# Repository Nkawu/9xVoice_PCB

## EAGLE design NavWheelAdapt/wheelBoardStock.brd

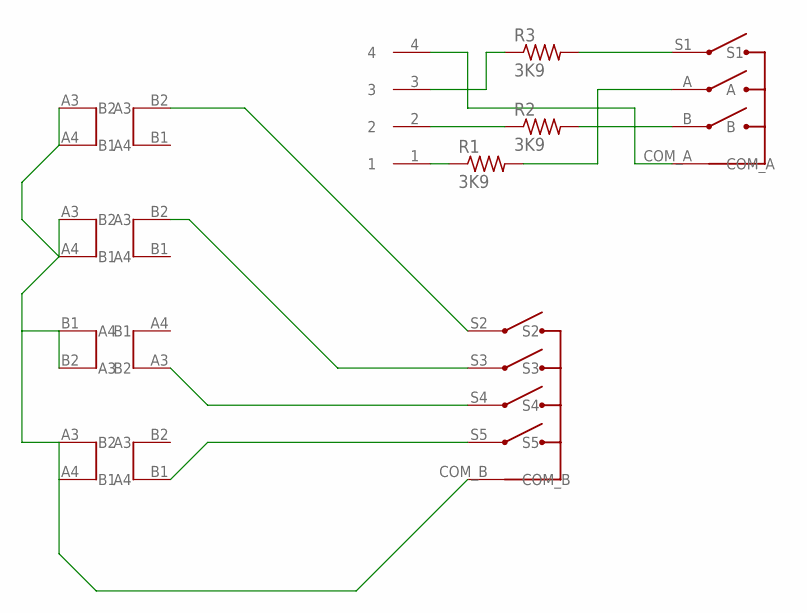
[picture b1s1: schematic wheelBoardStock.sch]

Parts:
R1, R2, R3: 3K9; R1206
U$1: TSWB-3N-CB222; W/DIREC
U$2, U$3, U$4, U$5: 9X_TACT_PATCH; 9XTACTPADS
U$6: 2MM_4P_HEADER; JST2MM_4P

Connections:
COM_A: U$1.COM_A, U$6.4
COM_B: U$1.COM_B, U$2.A3, U$2.A4, U$3.A3, U$3.A4, U$4.B1, U$4.B2, U$5.A3, U$5.A4
unnamed: R1.1, U$6.1
unnamed: R2.1, U$6.2
unnamed: R3.1, U$6.3
PHASE_A: R1.2, U$1.A
PHASE_B: R2.2, U$1.B
S2: U$1.S2, U$2.B2
S3: U$1.S3, U$3.B2
S4: U$1.S4, U$4.A3
S5: U$1.S5, U$5.B1
SELECT: R3.2, U$1.S1

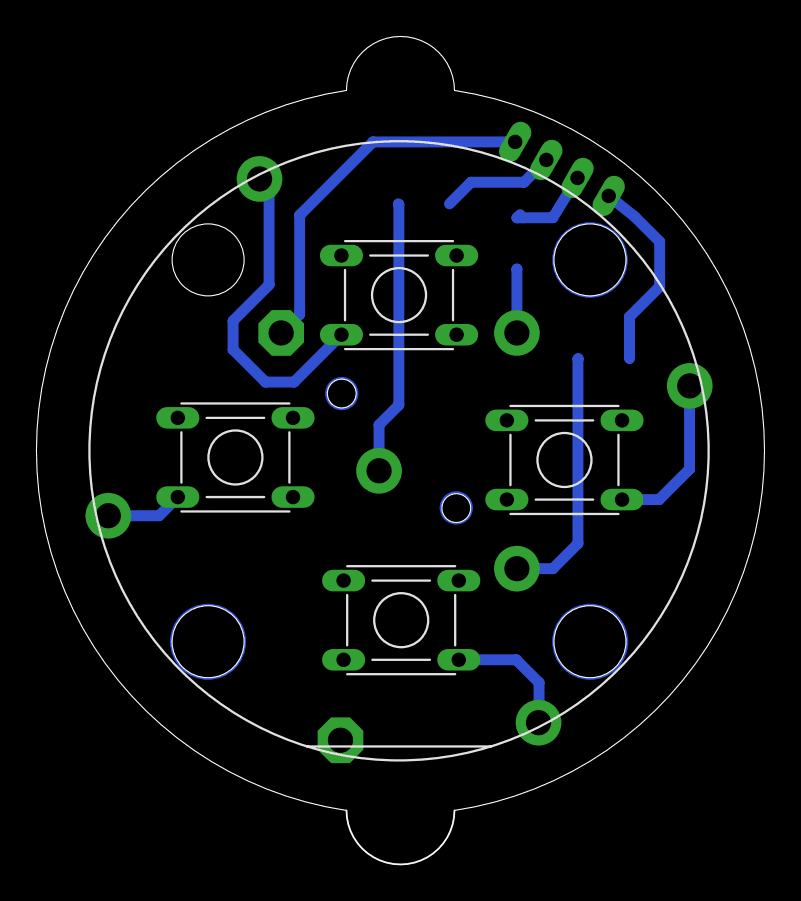
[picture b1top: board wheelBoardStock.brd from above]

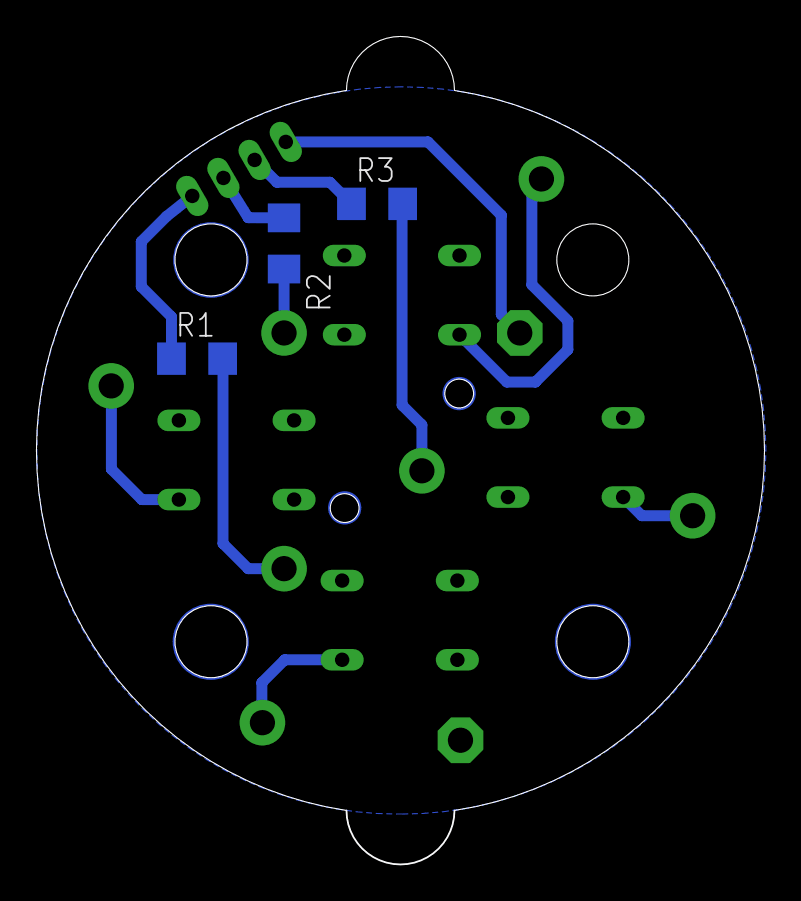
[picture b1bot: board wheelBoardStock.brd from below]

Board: 2 copper layers, 40.4 x 46.0 mm, 9 parts (3 on the bottom side), 12 nets.

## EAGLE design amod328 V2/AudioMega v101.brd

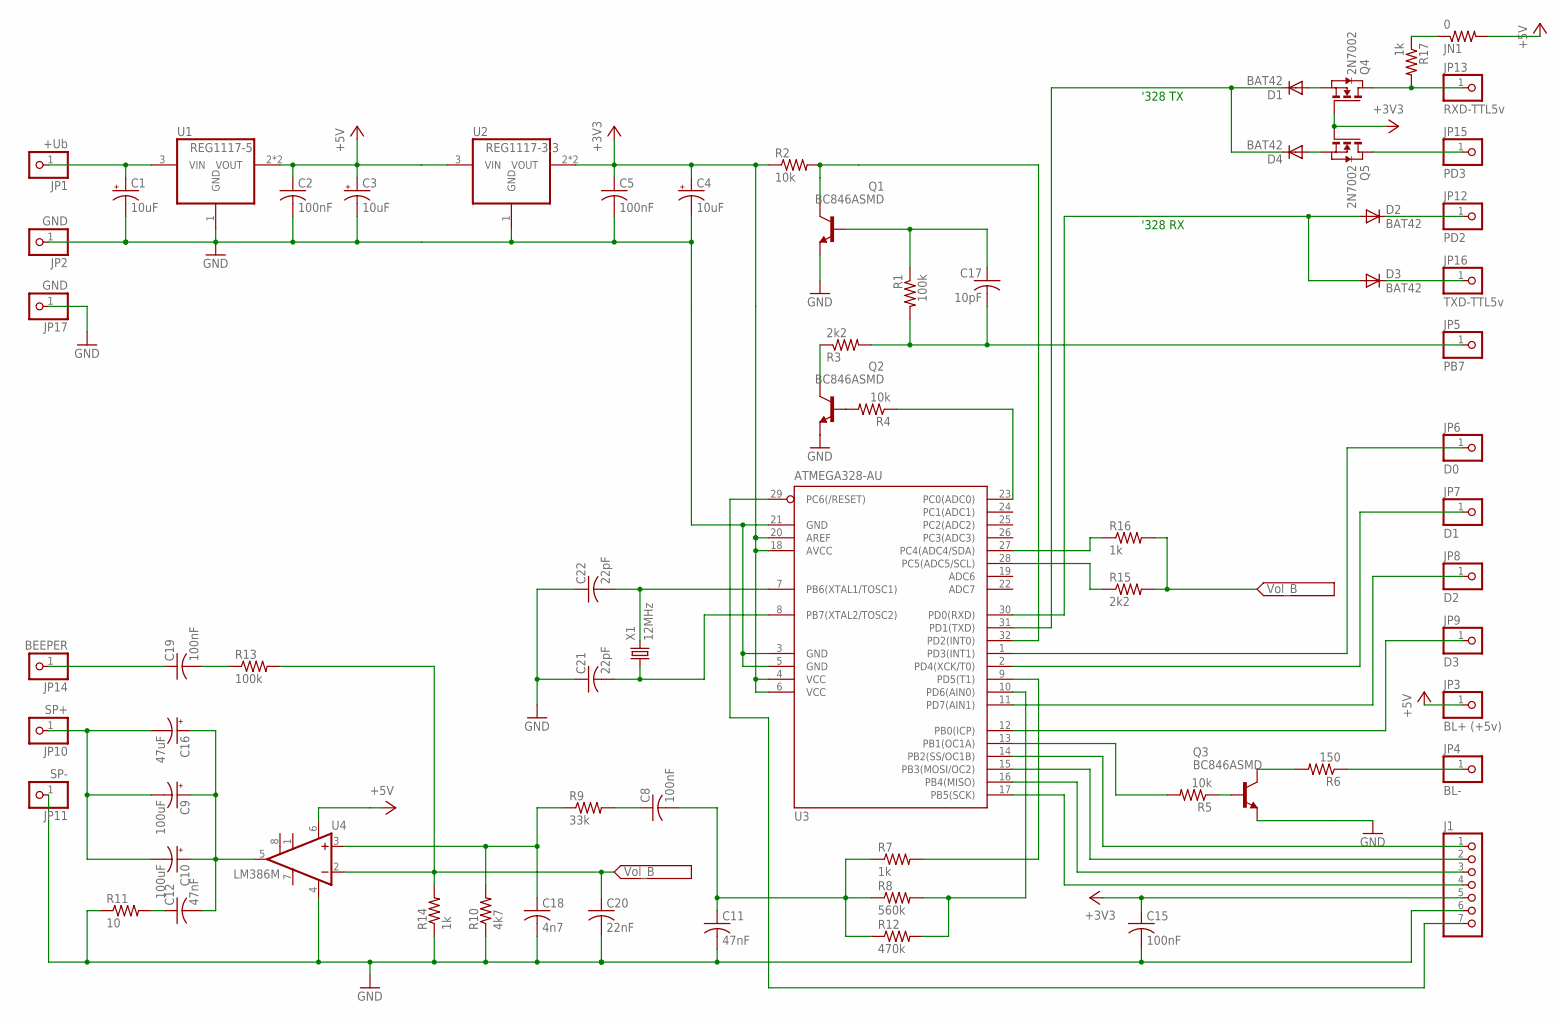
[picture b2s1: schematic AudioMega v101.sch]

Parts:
C1, C3, C4: 10uF; CT3528
C2, C5, C8, C15, C19: 100nF; C1206
C9, C10: 100uF; CT6032
C11, C12: 47nF; C1206
C16: 47uF; CT6032
C17: 10pF; C1206
C18: 4n7; C1206
C20: 22nF; C1206
C21, C22: 22pF; C1206
D1, D2, D3, D4: BAT42; SOD123
J1: PINHD-1X7; 1X07
JN1: 0; R1206
JP1: +Ub; 1X01
JP2, JP17: GND; 1X01
JP3: BL+ (+5v); 1X01
JP4: BL-; 1X01
JP5: PB7; 1X01
JP6: D0; 1X01
JP7: D1; 1X01
JP8: D2; 1X01
JP9: D3; 1X01
JP10: SP+; 1X01
JP11: SP-; 1X01
JP12: PD2; 1X01
JP13: RXD-TTL5v; 1X01
JP14: BEEPER; 1X01
JP15: PD3; 1X01
JP16: TXD-TTL5v; 1X01
Q1, Q2, Q3: BC846ASMD; SOT23
Q4, Q5: 2N7002; SOT-23
R1, R13: 100k; R1206
R2, R4, R5: 10k; R1206
R3, R15: 2k2; R1206
R6: 150; R1206
R7, R14, R16, R17: 1k; R1206
R8: 560k; R1206
R9: 33k; R1206
R10: 4k7; R1206
R11: 10; R1206
R12: 470k; R1206
U1: REG1117-5; SOT223
U2: REG1117-3.3; SOT223
U3: ATMEGA328-AU; TQFP32-08
U4: LM386M; SO08
X1: 12MHz; HC49UP

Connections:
+3V3: C4.+, C5.1, C15.1, J1.5, Q4.3 (G), Q5.3 (G), R2.1, U2.2 (VOUT), U2.4 (VOUT), U3.4 (VCC), U3.6 (VCC), U3.18 (AVCC), U3.20 (AREF)
+5V: C2.1, C3.+, JN1.2, JP3.1, U1.2 (VOUT), U1.4 (VOUT), U2.3 (VIN), U4.6 (VS)
B7: C17.2, JP5.1, R1.2, R3.2
CLK: Q1.3 (C), R2.2, U3.32 (PD2(INT0))
GND: C1.-, C2.2, C3.-, C4.-, C5.2, C11.2, C15.2, C18.2, C20.2, C21.1, C22.1, J1.6, JP2.1, JP11.1, JP17.1, Q1.2 (E), Q2.2 (E), Q3.2 (E), R10.1, R11.1, R14.1, U1.1 (GND), U2.1 (GND), U3.3 (GND), U3.5 (GND), U3.21 (GND), U4.4 (GND)
unnamed: R4.1, U3.23 (PC0(ADC0))
unnamed: D4.A, Q5.2 (S)
unnamed: J1.2, U3.15 (PB3(MOSI/OC2))
unnamed: J1.3, U3.16 (PB4(MISO))
unnamed: J1.4, U3.17 (PB5(SCK))
unnamed: J1.7, U3.29 (PC6(/RESET))
unnamed: C22.2, U3.7 (PB6(XTAL1/TOSC1)), X1.2
unnamed: C21.2, U3.8 (PB7(XTAL2/TOSC2)), X1.1
unnamed: Q2.1 (B), R4.2
unnamed: R16.1, U3.27 (PC4(ADC4/SDA))
unnamed: R15.1, U3.28 (PC5(ADC5/SCL))
unnamed: Q2.3 (C), R3.1
unnamed: C17.1, Q1.1 (B), R1.1
unnamed: C9.-, C10.-, C16.-, JP10.1
unnamed: C12.1, R11.2
unnamed: C9.+, C10.+, C12.2, C16.+, U4.5 (OUT)
unnamed: C18.1, R9.1, R10.2, U4.3 (+IN)
unnamed: C19.1, JP14.1
unnamed: C19.2, R13.1
unnamed: J1.1, U3.14 (PB2(SS/OC1B))
unnamed: JN1.1, R17.1
unnamed: C8.1, R9.2
unnamed: C8.2, C11.1, R7.1, R8.1, R12.1
unnamed: Q3.3 (C), R6.2
unnamed: R7.2, U3.9 (PD5(T1))
unnamed: R8.2, R12.2, U3.10 (PD6(AIN0))
unnamed: JP4.1, R6.1
unnamed: JP9.1, U3.12 (PB0(ICP))
unnamed: JP8.1, U3.11 (PD7(AIN1))
unnamed: C1.+, JP1.1, U1.3 (VIN)
unnamed: Q3.1 (B), R5.1
unnamed: R5.2, U3.13 (PB1(OC1A))
unnamed: JP7.1, U3.2 (PD4(XCK/T0))
unnamed: JP6.1, U3.1 (PD3(INT1))
unnamed: D3.C, JP16.1
unnamed: JP15.1, Q5.1 (D)
unnamed: D2.C, JP12.1
unnamed: JP13.1, Q4.1 (D), R17.2
unnamed: D2.A, D3.A, U3.30 (PD0(RXD))
unnamed: D1.A, Q4.2 (S)
unnamed: D1.C, D4.C, U3.31 (PD1(TXD))
VOL_B: C20.1, R13.2, R14.2, R15.2, R16.2, U4.2 (-IN)

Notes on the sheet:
'328 RX
'328 TX

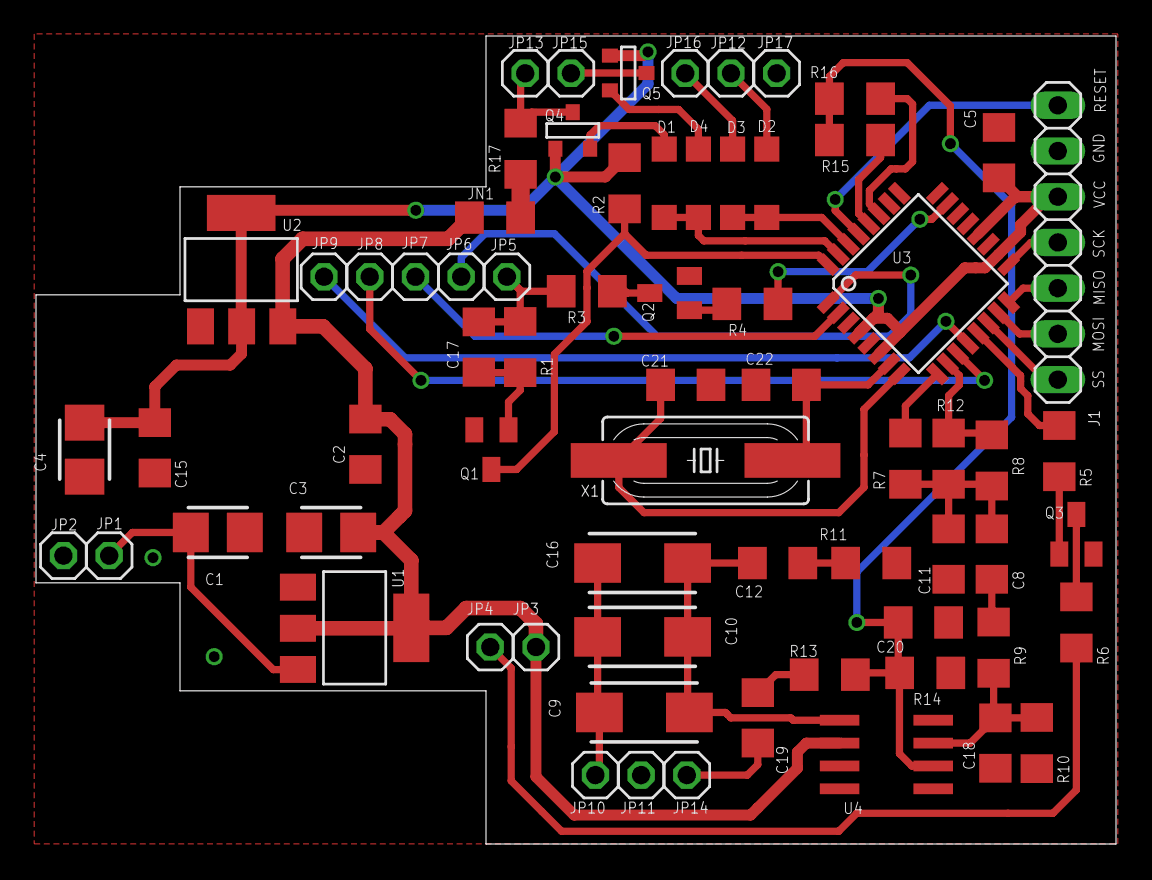
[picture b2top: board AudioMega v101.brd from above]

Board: 2 copper layers, 60.0 x 44.9 mm, 68 parts (0 on the bottom side), 47 nets.
